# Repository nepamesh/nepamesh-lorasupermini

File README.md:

# NEPAMesh LoraSupermini

A small carrier PCB that joins an nRF52840 "supermini" (Nice!Nano clone) to a Seeed Wio-SX1262 LoRa module, with an off-board 18650 cell and a 3D-printable case.  Core parts come to about $10 per node.  Part of the [NEPAMesh](https://nepamesh.com) community Meshtastic network.

**Status: v0.1, early.**  Boards are fabricated and one is partly assembled.  The Meshtastic variant is flashed on the first board, which sends and receives messages.  The MeshCore variants build but have not been flashed, and the case has not been sliced or printed.  Range has not been tested.

## What is in this repo

| Path | Contents |
|---|---|
| `nepamesh_lorasupermini.kicad_*` | KiCad 9 project: 2 layers, 32 x 55.5 mm |
| `lib/` | Project symbols and footprints (supermini, Wio-SX1262) |
| `gerbers/` | Gerber and drill files for JLCPCB (regenerated with the NEPAMesh LoraSupermini silkscreen and front logos; not fabricated in this form yet) |
| `3d/` | GLB models for viewers like [F3D](https://f3d.app): `nepamesh_lorasupermini.glb` is the bare board, `..._assembled.glb` adds approximate component bodies.  Regenerate with `tools/build_3d.py` |
| `tools/build.py` | Generates the KiCad project from code.  Edit the script, not the generated files |
| `tools/fill.py`, `tools/logo.py` | Zone fill and logo tracing |
| `case/build_case.py` | build123d script for the two-part case (62.2 x 87.8 mm).  Outputs in `case/out/` as STL |
| `firmware/meshtastic/` | Meshtastic variant (see its README) |
| `firmware/meshcore/` | MeshCore variant: repeater, room server, USB and BLE companion |
| `firmware/flash.sh` | Serial DFU flashing helper |

## Hardware summary

- Power: 18650 into a JST-PH connector, a PTC fuse, and a P-channel MOSFET for reverse-polarity protection, then the supermini battery input.  The module takes 3.3 V from the supermini VCC pin.
- No battery divider, button, GPS or I2C on the board.  The firmware variants map spare pins for bodge wiring.
- Pin map (Wio-SX1262 to nRF52840): SCK P0.02, MOSI P1.15, MISO P1.13, NSS P1.06, NRST P1.04, BUSY P0.31, DIO1 P0.29, RF_SW P1.11.  DIO2 switches TX inside the module, and DIO3 powers its TCXO at 1.8 V.

## Firmware

Build the Meshtastic variant by copying `firmware/meshtastic/variants/nrf52840/diy/nepamesh_lorasupermini` into a checkout of [meshtastic/firmware](https://github.com/meshtastic/firmware) and running `pio run -e nepamesh_lorasupermini`.  The MeshCore variant goes into `variants/` of a checkout of [meshcore-dev/MeshCore](https://github.com/meshcore-dev/MeshCore).  Meshtastic 2.8.3 is built and running on hardware.  MeshCore commit 75b04ef builds only and has not been flashed.

Flash by double-tapping RST to GND so the bootloader drive appears, then copy the `.uf2` or use `firmware/flash.sh`.

Read before you flash:

- **Default credentials.**  The MeshCore repeater and room server builds ship with the admin password `password` and the room password `hello`.  The BLE companion build uses the pairing PIN `123456`.  Change them before putting a node on the air.  They are placeholders from upstream defaults, not secrets.
- **Set a region first.**  Meshtastic does not transmit until a region is set.
- **Fit the antenna before powering up.**  Transmitting into an open antenna port can damage the SX1262.
- **Licenses.**  The Meshtastic variant is a derivative of GPL-3.0 code and is distributed under GPL-3.0.  The MeshCore variant is MIT, and its `variant.h` retains a Seeed K.K. MIT header.  The Meshtastic hardware model reports as `PRIVATE_HW`.

## Known gaps

- Supermini hole drill and outline were assumed from photos and a datasheet.  Measure the real board before ordering more.
- The supermini VCC pin has not been checked against 125 mA transmit bursts.
- The first five boards were fabricated with the working name "meschoresupermini" on the silkscreen.  The files here use the new name and add two small NEPAMesh logos on the front.  The finest logo strokes are thinner than JLCPCB's usual 0.15 mm silkscreen minimum, so expect fuzzy detail.

## License

Original files outside `firmware/` are MIT (see `LICENSE`).  Firmware variants follow the licenses in `firmware/meshtastic/LICENSE` and `firmware/meshcore/LICENSE`.  The NEPAMesh logo is not covered.

*NEPAMesh is a community Meshtastic network covering Northeastern Pennsylvania's Wyoming Valley.  Live map at [map.nepamesh.com](https://map.nepamesh.com).  Questions in the [Discord](https://discord.com/invite/cSpfk6H2hz).*

*[Meshtastic](https://meshtastic.org) is a registered trademark of Meshtastic LLC.  No warranty is provided.  Use at your own risk.  This project is not endorsed by or affiliated with Meshtastic LLC.*

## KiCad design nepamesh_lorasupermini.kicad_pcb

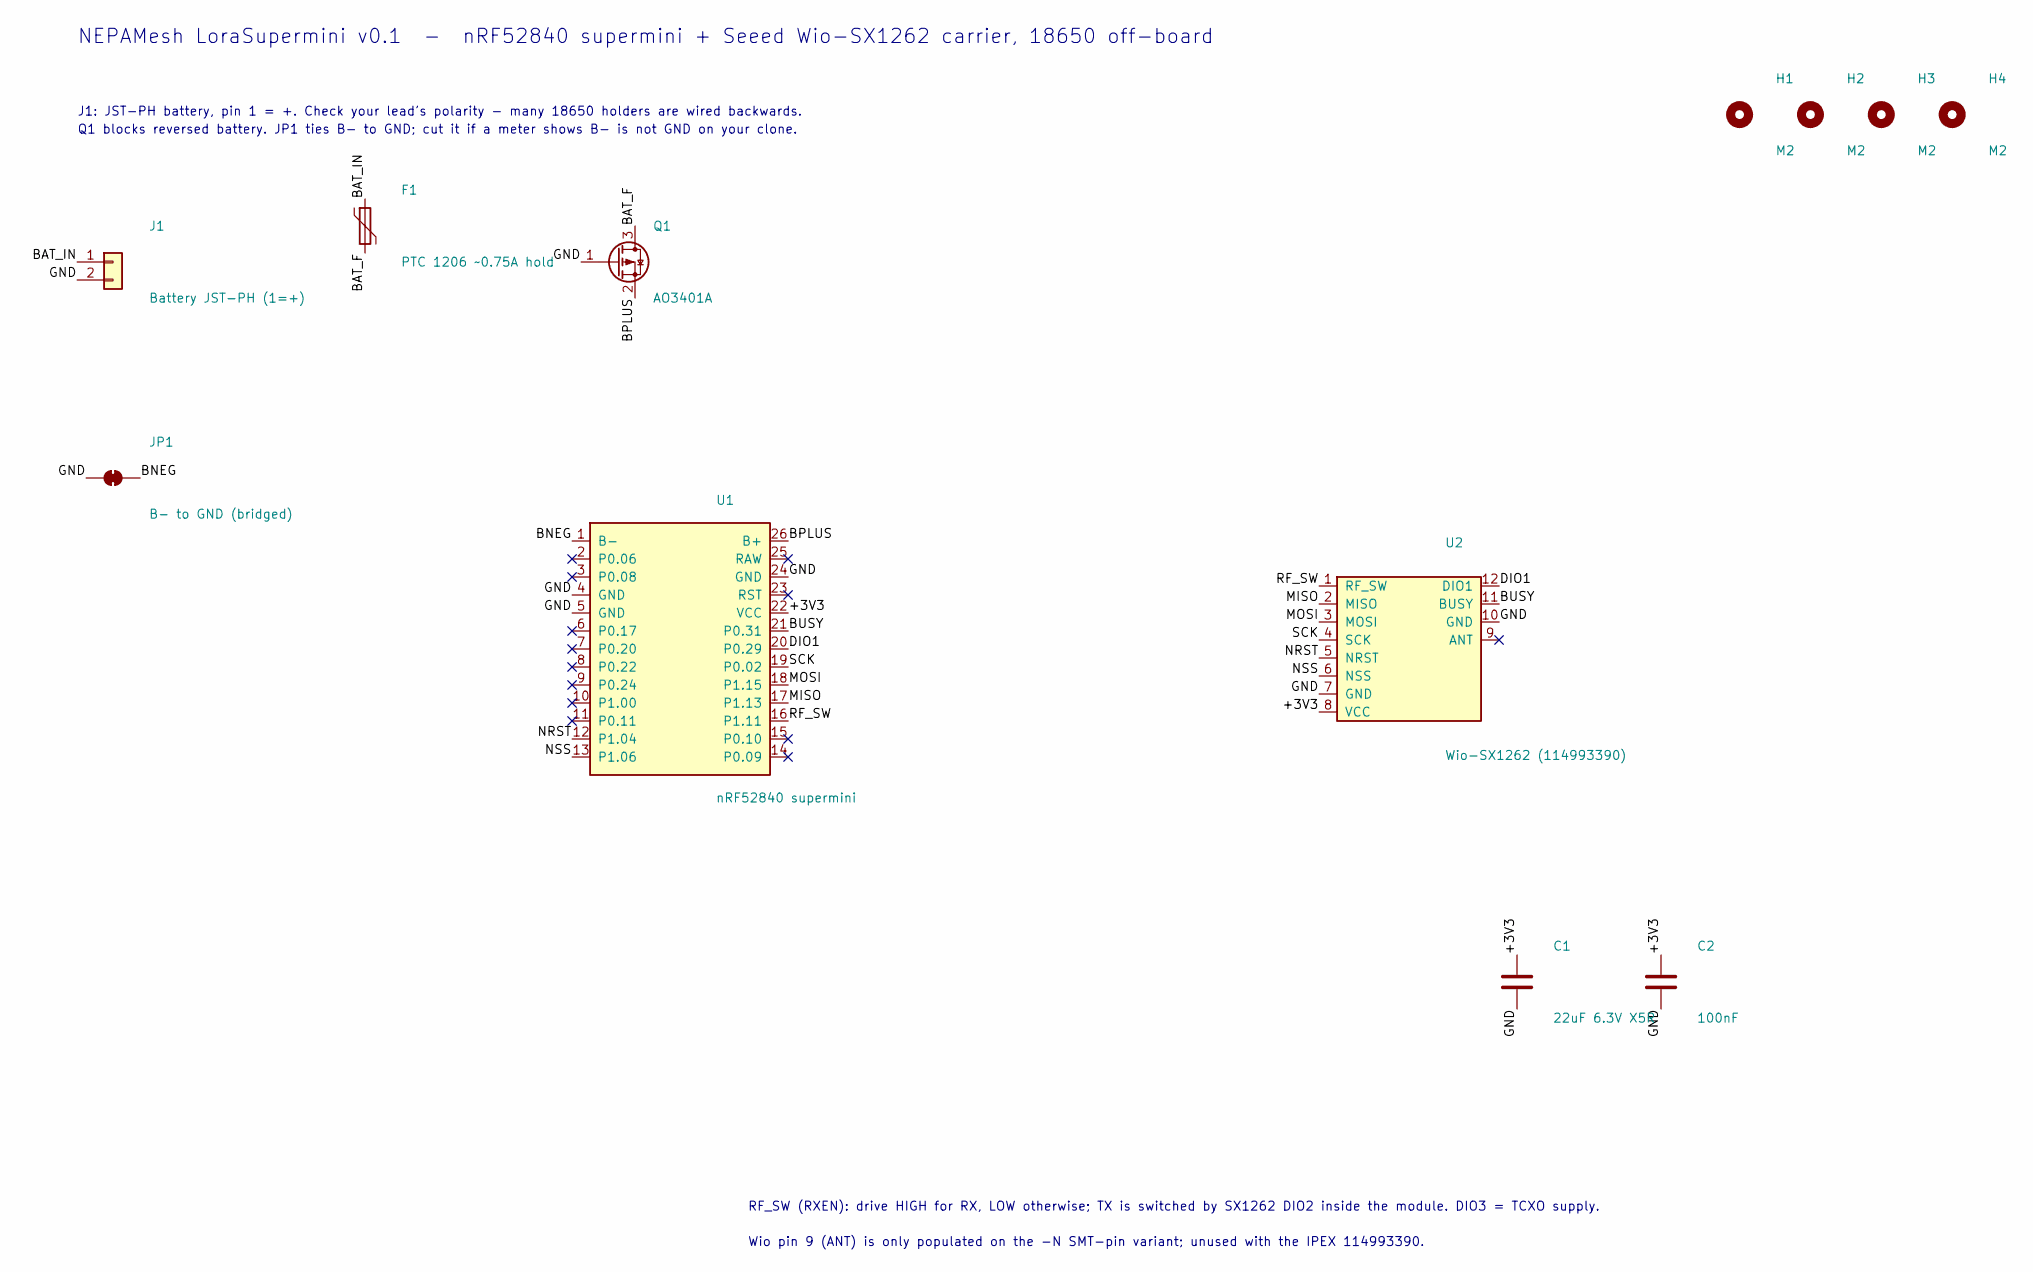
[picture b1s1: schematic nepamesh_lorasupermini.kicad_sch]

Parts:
C1: 22uF 6.3V X5R; C_0805_2012Metric
C2: 100nF; C_0603_1608Metric
F1: PTC 1206 ~0.75A hold; Fuse_1206_3216Metric
H1, H2, H3, H4: M2; MountingHole_2.2mm_M2
J1: Battery JST-PH (1=+); JST_PH_B2B-PH-K_1x02_P2.00mm_Vertical
JP1: B- to GND (bridged); SolderJumper-2_P1.3mm_Bridged_Pad1.0x1.5mm
Q1: AO3401A; SOT-23
U1: nRF52840 supermini; Supermini_nRF52840_THT
U2: Wio-SX1262 (114993390); Wio-SX1262_Seeed

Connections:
/+3V3: C1.1, C2.1, U1.22 (VCC), U2.8 (VCC)
/BAT_F: F1.2, Q1.3 (D)
/BAT_IN: F1.1, J1.1
/BNEG: JP1.2 (B), U1.1 (B-)
/BPLUS: Q1.2 (S), U1.26 (B+)
/BUSY: U1.21 (P0.31), U2.11 (BUSY)
/DIO1: U1.20 (P0.29), U2.12 (DIO1)
/GND: C1.2, C2.2, J1.2, JP1.1 (A), Q1.1 (G), U1.4 (GND), U1.5 (GND), U1.24 (GND), U2.7 (GND), U2.10 (GND)
/MISO: U1.17 (P1.13), U2.2 (MISO)
/MOSI: U1.18 (P1.15), U2.3 (MOSI)
/NRST: U1.12 (P1.04), U2.5 (NRST)
/NSS: U1.13 (P1.06), U2.6 (NSS)
/RF_SW: U1.16 (P1.11), U2.1 (RF_SW)
/SCK: U1.19 (P0.02), U2.4 (SCK)

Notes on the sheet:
NEPAMesh LoraSupermini v0.1 - nRF52840 supermini + Seeed Wio-SX1262 carrier, 18650 off-board
J1: JST-PH battery, pin 1 = +. Check your lead's polarity - many 18650 holders are wired backwards.
Q1 blocks reversed battery. JP1 ties B- to GND; cut it if a meter shows B- is not GND on your clone.
RF_SW (RXEN): drive HIGH for RX, LOW otherwise; TX is switched by SX1262 DIO2 inside the module. DIO3 = TCXO supply.
Wio pin 9 (ANT) is only populated on the -N SMT-pin variant; unused with the IPEX 114993390.

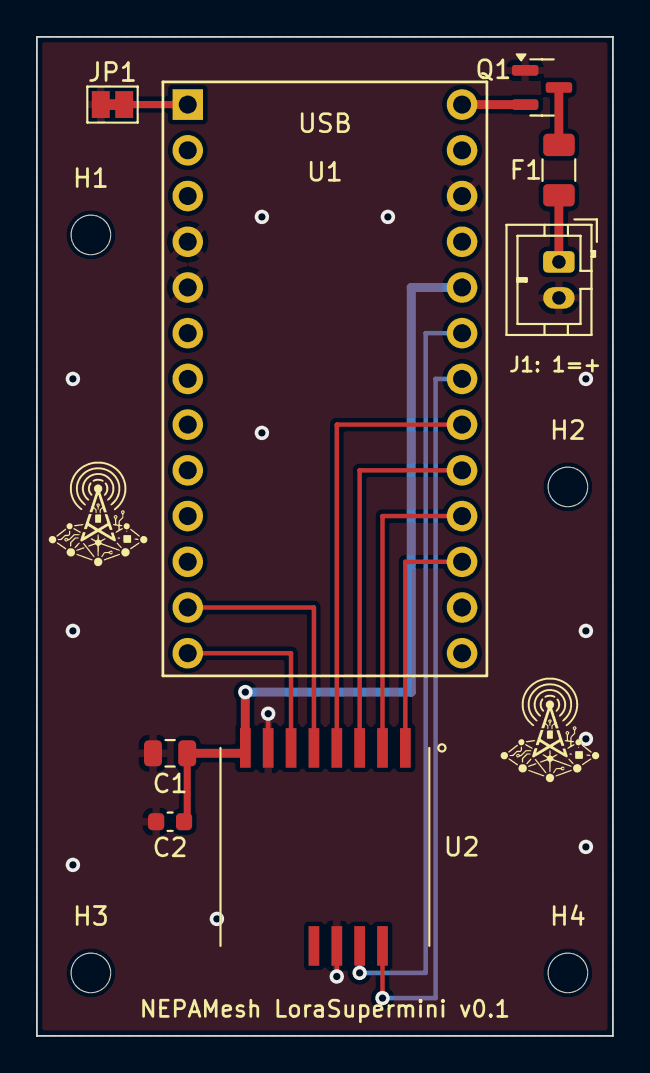
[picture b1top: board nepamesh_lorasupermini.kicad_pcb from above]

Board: 2 copper layers, 32.0 x 55.5 mm, 12 parts (0 on the bottom side), 14 nets.
